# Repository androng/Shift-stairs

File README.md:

Shift-stairs
============

Code for stair lights controller

The Arduino code is in the pde file.

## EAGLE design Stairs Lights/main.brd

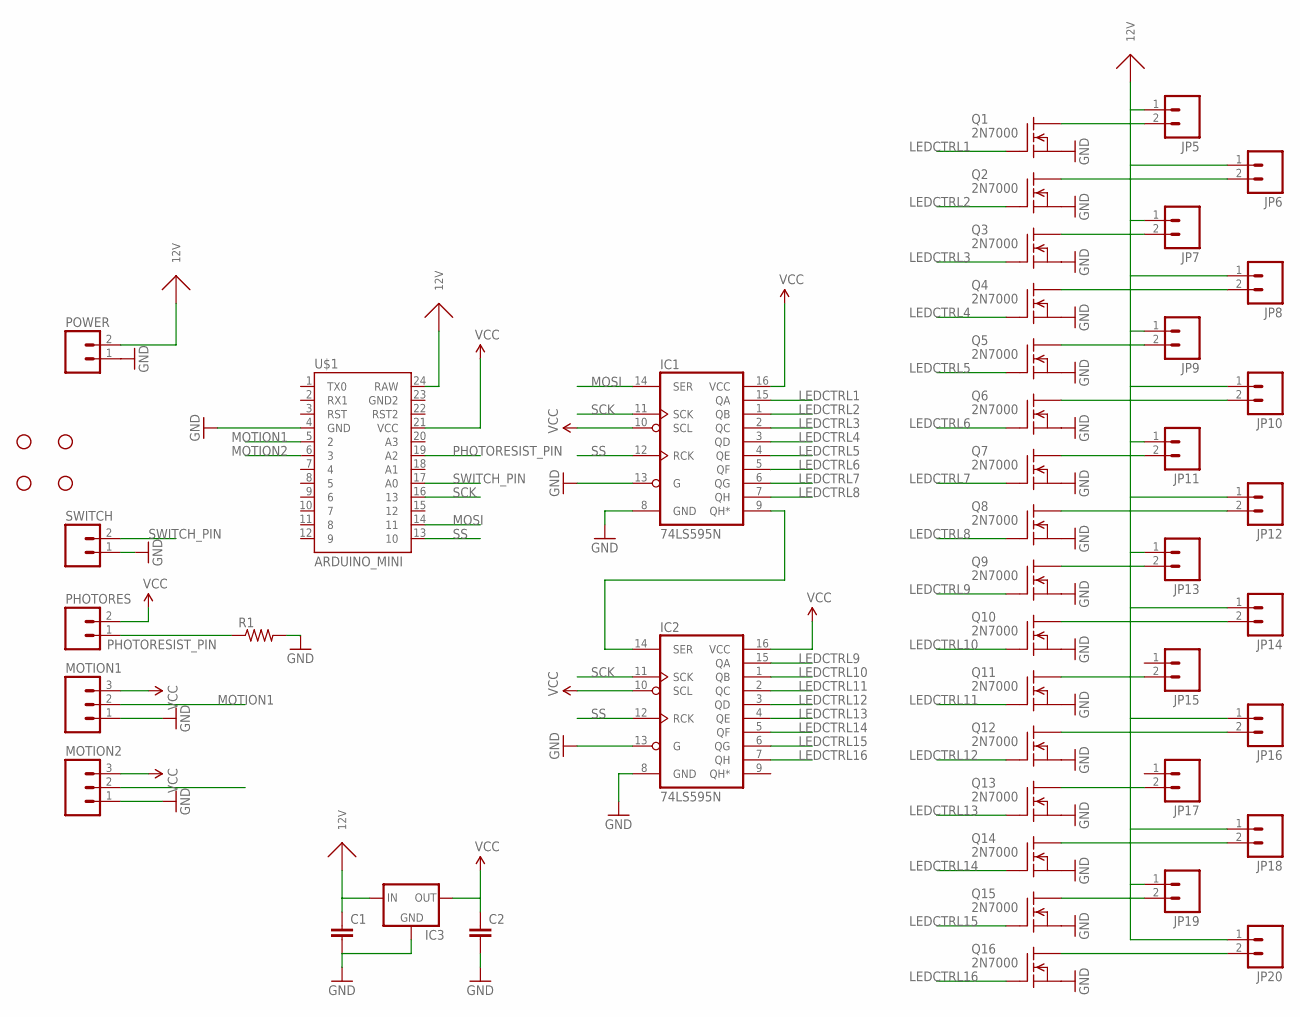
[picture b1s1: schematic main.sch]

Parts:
C1, C2: CAPKIT; CAP-PTH-SMALL-KIT
IC1, IC2: 74LS595N; DIL16
IC3: V_REG_78XXSINK; TO220-IGO
JP1, JP2, JP3, JP4: STAND-OFF
JP5, JP6, JP7, JP8, JP9, JP10, JP11, JP12, JP13, JP14, JP15, JP16, JP17, JP18, JP19, JP20: M02PTH; 1X02
MOTION1, MOTION2: M03PTH; 1X03
PHOTORES: M02PTH; 1X02
POWER: M025MM; SCREWTERMINAL-5MM-2
Q1, Q2, Q3, Q4, Q5, Q6, Q7, Q8, Q9, Q10, Q11, Q12, Q13, Q14, Q15, Q16: 2N7000; TO92
R1: RESISTORAXIAL-0.3; AXIAL-0.3
SWITCH: M02PTH; 1X02
U$1: ARDUINO_MINI

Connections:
12V: C1.1, IC3.IN, JP5.1, JP6.1, JP7.1, JP8.1, JP9.1, JP10.1, JP11.1, JP12.1, JP13.1, JP14.1, JP16.1, JP18.1, JP19.1, JP20.1, POWER.2, U$1.24 (RAW)
GND: C1.2, C2.2, IC1.8 (GND), IC1.13 (G), IC2.8 (GND), IC2.13 (G), IC3.GND, MOTION1.1, MOTION2.1, POWER.1, Q1.1 (S), Q2.1 (S), Q3.1 (S), Q4.1 (S), Q5.1 (S), Q6.1 (S), Q7.1 (S), Q8.1 (S), Q9.1 (S), Q10.1 (S), Q11.1 (S), Q12.1 (S), Q13.1 (S), Q14.1 (S), Q15.1 (S), Q16.1 (S), R1.P$2 (2), SWITCH.1, U$1.4 (GND)
LEDCTRL1: IC1.15 (QA), Q1.2 (G)
LEDCTRL2: IC1.1 (QB), Q2.2 (G)
LEDCTRL3: IC1.2 (QC), Q3.2 (G)
LEDCTRL4: IC1.3 (QD), Q4.2 (G)
LEDCTRL5: IC1.4 (QE), Q5.2 (G)
LEDCTRL6: IC1.5 (QF), Q6.2 (G)
LEDCTRL7: IC1.6 (QG), Q7.2 (G)
LEDCTRL8: IC1.7 (QH), Q8.2 (G)
LEDCTRL9: IC2.15 (QA), Q9.2 (G)
LEDCTRL10: IC2.1 (QB), Q10.2 (G)
LEDCTRL11: IC2.2 (QC), Q11.2 (G)
LEDCTRL12: IC2.3 (QD), Q12.2 (G)
LEDCTRL13: IC2.4 (QE), Q13.2 (G)
LEDCTRL14: IC2.5 (QF), Q14.2 (G)
LEDCTRL15: IC2.6 (QG), Q15.2 (G)
LEDCTRL16: IC2.7 (QH), Q16.2 (G)
MOSI: IC1.14 (SER), U$1.14 (11)
MOTION1: MOTION1.2, U$1.5 (2)
MOTION2: MOTION2.2, U$1.6 (3)
unnamed: IC1.9 (QH*), IC2.14 (SER)
unnamed: JP5.2, Q1.3 (D)
unnamed: JP6.2, Q2.3 (D)
unnamed: JP7.2, Q3.3 (D)
unnamed: JP8.2, Q4.3 (D)
unnamed: JP9.2, Q5.3 (D)
unnamed: JP10.2, Q6.3 (D)
unnamed: JP11.2, Q7.3 (D)
unnamed: JP12.2, Q8.3 (D)
unnamed: JP13.2, Q9.3 (D)
unnamed: JP14.2, Q10.3 (D)
unnamed: JP15.2, Q11.3 (D)
unnamed: JP16.2, Q12.3 (D)
unnamed: JP17.2, Q13.3 (D)
unnamed: JP18.2, Q14.3 (D)
unnamed: JP20.2, Q16.3 (D)
unnamed: JP19.2, Q15.3 (D)
PHOTORESIST_PIN: PHOTORES.1, R1.P$1 (1), U$1.19 (A2)
SCK: IC1.11 (SCK), IC2.11 (SCK), U$1.16 (13)
SS: IC1.12 (RCK), IC2.12 (RCK), U$1.13 (10)
SWITCH_PIN: SWITCH.2, U$1.17 (A0)
VCC: C2.1, IC1.10 (SCL), IC1.16 (VCC), IC2.10 (SCL), IC2.16 (VCC), IC3.OUT, MOTION1.3, MOTION2.3, PHOTORES.2, U$1.21 (VCC)

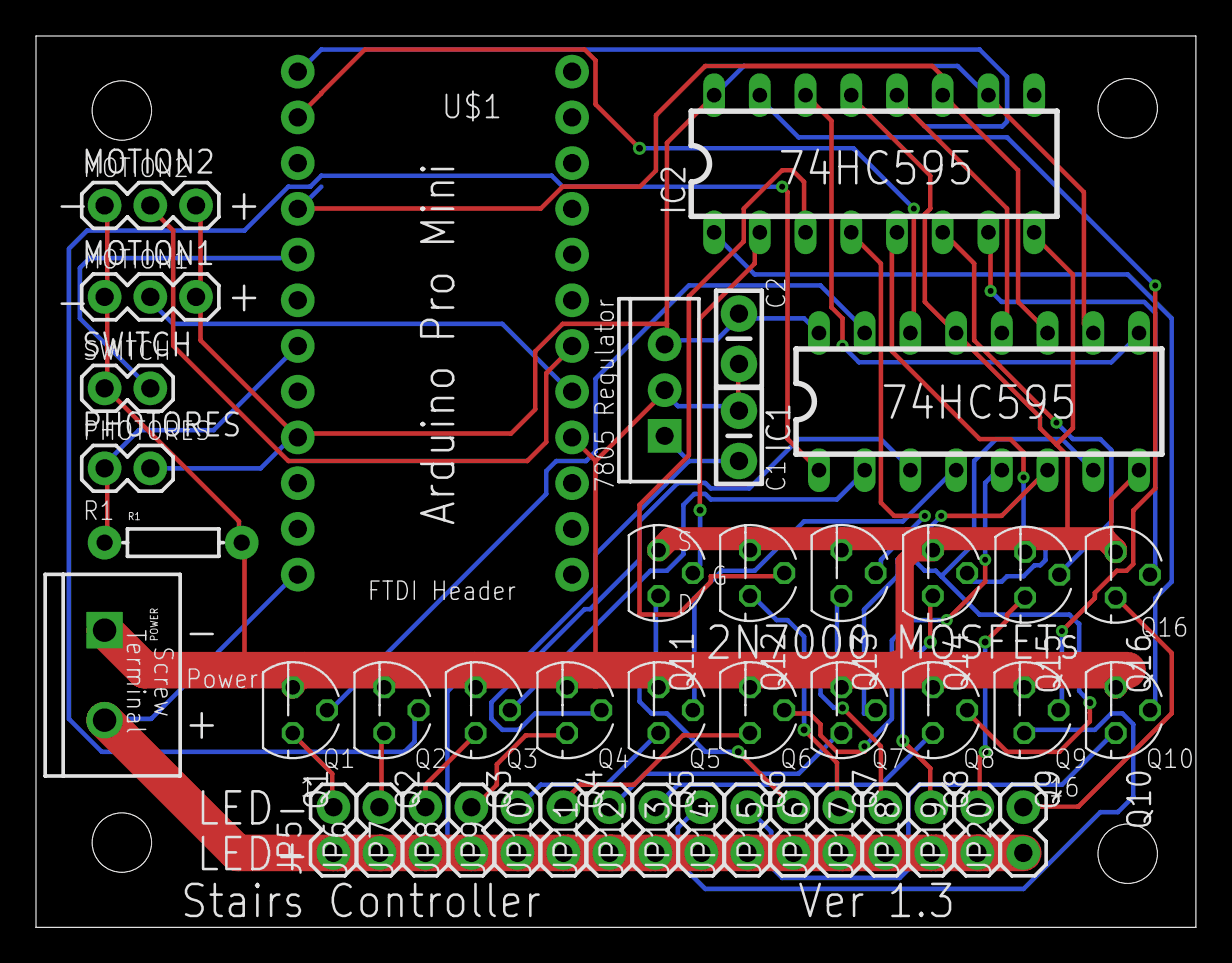
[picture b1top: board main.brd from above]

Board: 2 copper layers, 64.4 x 49.5 mm, 48 parts (0 on the bottom side), 43 nets.

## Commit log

2011-08-24 First commit. Lights constantly cycle
2011-08-24 Switch override added in software. No interrupts.
2011-08-24 Shortened turnon/off duration, added motion sensor interrupt turn on/off.
2011-08-25 Added photoresistor support so that the circuit will not turn on when it is bright.
2011-08-26 Added a warm-up time and increased light threshold so that lights do not turn on in the daytime.
2013-07-22 Refactored into state machine format
2013-07-22 Cleaned up some debug outputs and removed expoDutyCycles
2013-07-22 Changed to say "pde"
2013-07-29 Added Eagle Board Files
2013-07-29 Added note about program memory.
2014-10-12 Renamed Shift_stairs to ion file and added legacy ShiftPWM library
2014-11-10 Changed PCB to V1.1, fixed backwards transistor problem
2015-02-09 Updated to version 1.2
2015-03-30 Added code for banisters on pin 14 and 15
2015-06-16 1.3 Fixed photoresistor hardware problem
2015-06-18 Changed some layers in 1.3
2016-01-20 Photoresistor was mandatory before. Now it's optional.
2016-10-07 Added code and changed pin numbers to read all the new switches and control the shift registers on the v5 PCB
2016-10-07 Changed numLEDs to be a variable according to a switch
2017-05-15 V6 PCB Added function to detect the switches Added function to detect the dials
2017-06-03 Added function to calculate what time the steps should turn on
2017-06-04 Changed state machine to use time for brightness instead of “ticks”
2017-06-05 Made the dials restart the animation Made brightness and propagate speed more linear Refactored some variable names
2017-06-19 Added “end steps always on” switch logic Changed direction of brightness knob to intended direction Corrected “bottom to top” and “top to bottom” directions Changed logic levels of motion detector pi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
2017-06-19 Made motion detectors positive logic
2017-08-10 V7 turn on pull up resistors
2018-05-22 Converted motion detector pins to negative logic
2018-05-27 Changed MO2 pin to match Board v7 and changed "on time" to match motion detectors

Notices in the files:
parts and their libraries:
SparkFun: Licensing: CC v3.0 Share-Alike You are welcome to use this library for commercial purposes.
